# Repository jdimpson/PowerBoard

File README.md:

# PowerBoard Redux PCB

These are the Eage CAD Schematics and Board files, plus the Gerbers of some boards as-built, of an AdaFruit PowerBoost 1000C (https://www.adafruit.com/product/2465) adapted to the Raspberry Pi Zero form factor. It provides power to the +5VDC pins of the RPi header (protected via Schottkey diode). As AdaFruit describes the product this is based on, "With a built-in load-sharing battery charger circuit, you'll be able to keep your power-hungry project running even while recharging the battery!"

See also the PowerHolder board (https://github.com/jdimpson/PowerHolder) which is just like this one, but has battery clips to hold a Li Ion 18650 cell on the board, rather than fussing with JST connectors. It also provides a way to use a stock PowerBoost 10000C board so you don't have as much soldering to do.

The board patches the Low Battery (LBO) signal to the Pi via a level shifter, and also adds a programmable tactile button and LED.  You can use either one of those ubiquitous square tactile / momentary buttons, or one that mounts vertically (https://www.digikey.com/product-detail/en/te-connectivity-alcoswitch-switches/1825027-5/450-1662-ND/529484). The footprints for the two buttons overlap, which looks ugly and means you really can choose only one. It also provides a spot for a vertical slide switch that enables or disables the power circuit (https://www.digikey.com/product-detail/en/c-k/OS102011MA1QN1/CKN9559-ND/1981430). It's possible to find horizontal slide switch that fits in the same footprint. (I've only ordered them from ebay.)

Python software that works with the LBO signal, button, and LED are available in the [RPiIoT](https://github.com/jdimpson/RPiIoT) repo.

The MicroUSB connector is not the same foot print as AdaFruit uses in their PowerBoost, because I couldn't figure out which one it was. The part I use is an amphenol 10118194-0001LF (https://www.digikey.com/product-detail/en/amphenol-icc-fci/10118194-0001LF/609-4618-1-ND/2785382). It still has 4 through-hole-ish studs for strength (but can be hot-air reflowed) like AdaFruit's part, but the location of the studs are incompatible.

Battery is connected to a JST-style connector in a manner compatible with how AdaFruit does their polarity, or you can omit the connector and use the 2.54 mm pitch througholes to solder wires or a different connector to. Note that another Repo contains the PowerCarrier board, which is functionally identical to this board, but includes battery holders for a Li-Ion 18650 cell on the board.

Changelog
- Before v1.0 / Redux, I didn't know what I was doing, and kept laying out boards with traces that were way too small for the currents involved. 
- v1.01: Thickened VBAT, VLIPO, and USB traces from circuit to aux header; added zener diode to 5V trace into RPi; using VBAT rather than VLIPO in ENABLE pin switch. 

TODO:
- do over that preserve original PowerBoost footprint so that you can either reflow the board or just pop one of AdaFruit's board onto it. 

Raspberry Pi Pins used:

- GPIO17/Phy11 is connected to a momentary / tactile switch. Available for arbitrary software control (typically running my powerboard.py and associated code).
- GPIO27/Phy13 is connected to a resistor and then an LED. Available for arbitrary software control (e.g. flashing to show grace period, and typically running my powerboard.py and associated code).
- GPIO26/Phy37 is connected to via transistor and appropriate hold up resistor to the LBO signal of the PowerBoost circuit. This is how the Raspberry Pi knows to shut down. The signal is held at battery level (but level shifted to 3.3 V before hitting the RPi) until the Li Ion battery level drops below 3.4VDC (or maybe it's 3.2V, I forget) at which point the LBO signal drops to ground. This tells the software on the RPi to do a graceful shutdown.

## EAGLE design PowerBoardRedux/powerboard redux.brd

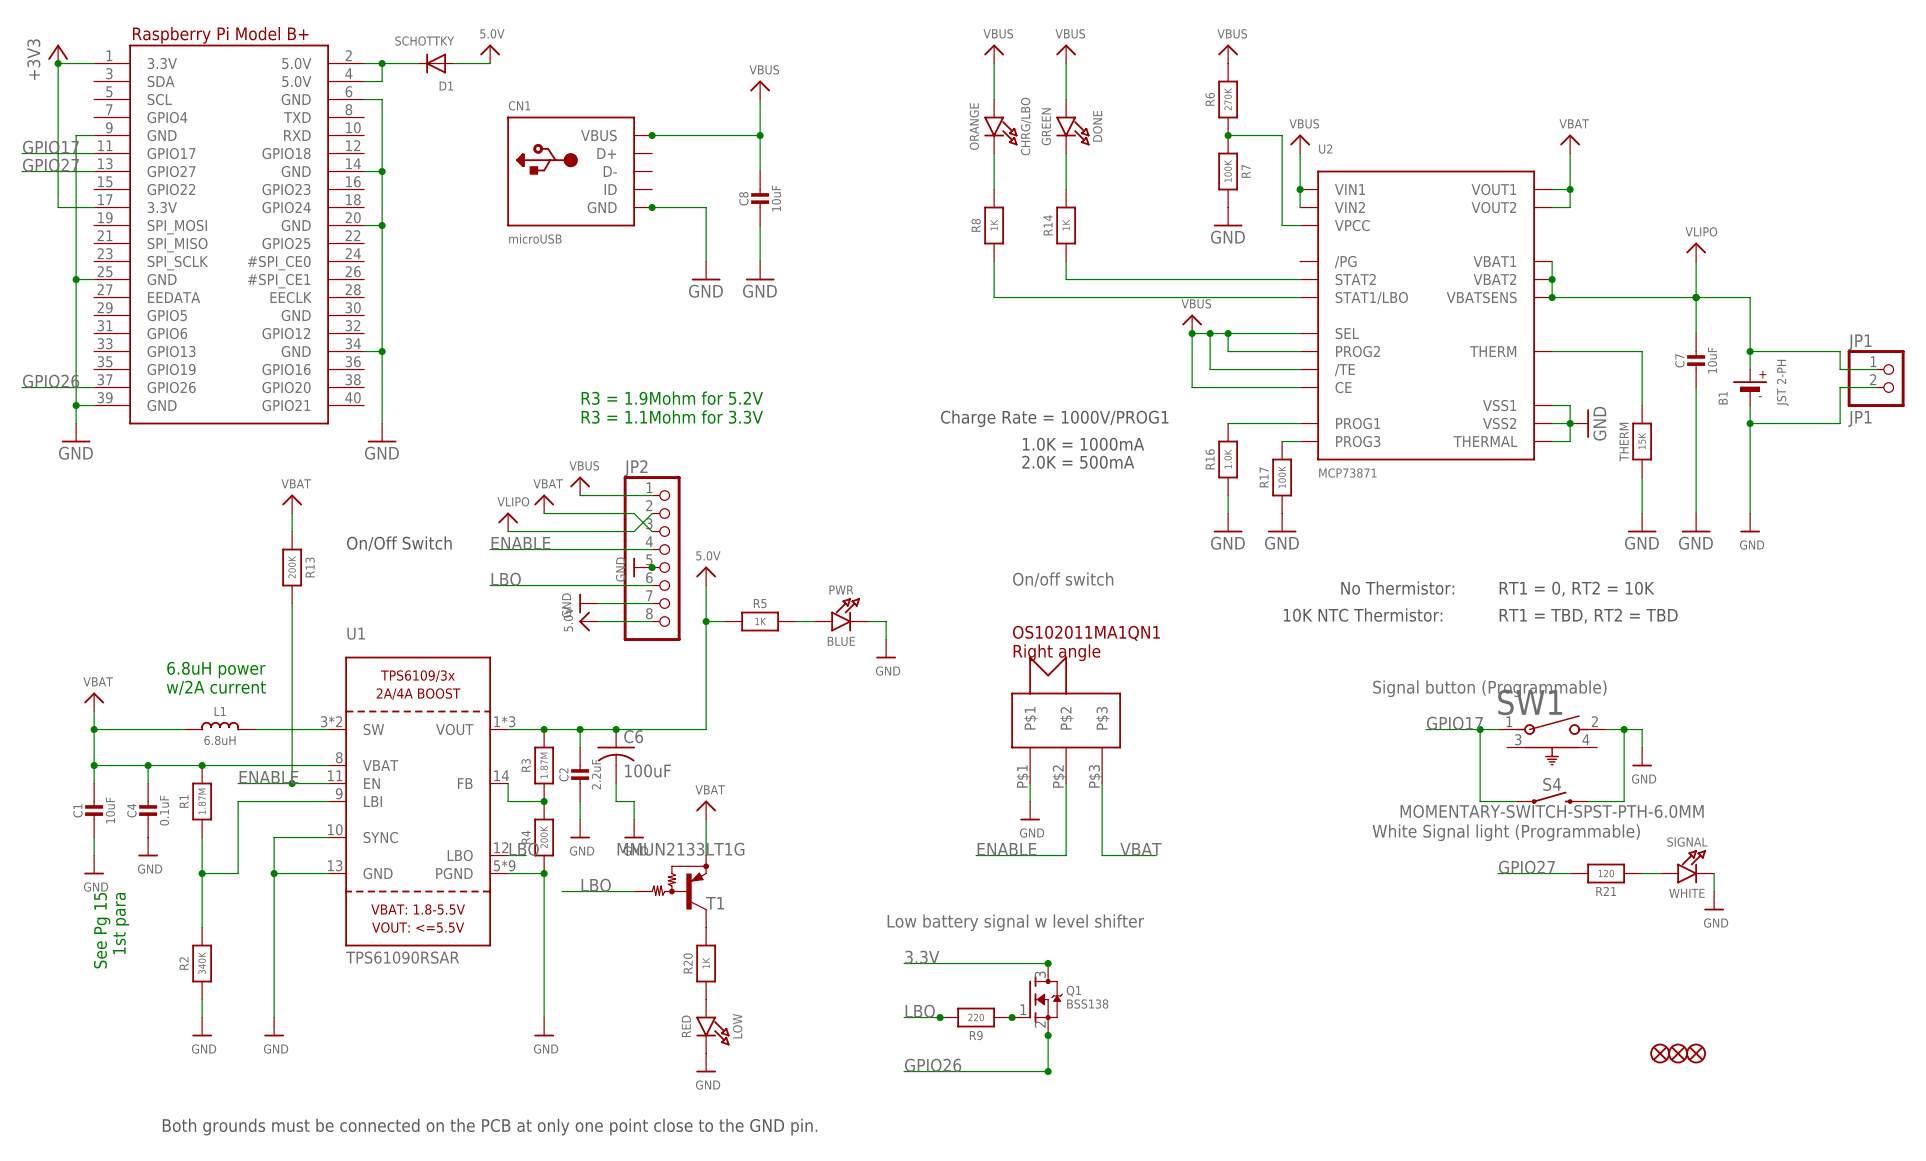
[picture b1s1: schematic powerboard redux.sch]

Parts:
B1: JST 2-PH; JSTPH2
C1, C7, C8: 10uF; 0805-NO@1
C2: 2.2uF; 0805-NO@1
C4: 0.1uF; 0805_10MGAP
C6: 100uF; C1210
CHRG/LBO: ORANGE; CHIPLED_0805_NOOUTLINE
CN1: microUSB; 4UCONN_20329
D1: SCHOTTKY; SOD-123FL
DONE: GREEN; CHIPLED_0805_NOOUTLINE
FID1, FID2, FID3: FIDUCIAL""; FIDUCIAL_1MM
JP1: JP1; 1X02_ROUND
JP2: HEADER-1X8ROUND; 1X08_ROUND
L1: 6.8uH; INDUCTOR_5X5MM_TDK_VLC5045
LOW: RED; CHIPLED_0805_NOOUTLINE
PWR: BLUE; CHIPLED_0805_NOOUTLINE
Q1: BSS138; SOT23-R
R1: 1.87M; _0805MP
R2: 340K; _0805MP
R3: 1.87M; 0805-NO
R4, R13: 200K; 0805-NO
R5, R8, R14, R20: 1K; 0805-NO
R6: 270K; 0805-NO
R7, R17: 100K; 0805-NO
R9: 220; 0805-NO
R16: 1.0K; 0805-NO
R21: 120; 0805-NO
RPI1: RASPBERRYPI_BPLUS_BONNETNODIM; PI_BONNET_NODIM
S4: MOMENTARY-SWITCH-SPST-PTH-6.0MM; TACTILE_SWITCH_PTH_6.0MM
SIGNAL: WHITE; CHIPLED_0805_NOOUTLINE
SW1: 1825027-5; SW2_1825027-A
SW2: OS102011MA1QN1
T1: MMUN2133LT1G; SC59-BEC
THERM: 15K; 0805-NO
U1: TPS61090RSAR; PVQFN-16
U2: MCP73871; QFN20_4MM

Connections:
3.3V: Q1.3 (D), RPI1.1 (3.3V), RPI1.17 (3.3V)
5.0V: C2.1, C6.1, D1.A, JP2.8, R3.2, R5.1, U1.1 (VOUT), U1.15 (VOUT), U1.16 (VOUT)
5.0V@1: D1.C, RPI1.2 (5.0V), RPI1.4 (5.0V)
ENABLE: JP2.4, R13.2, SW2.P$2, U1.11 (EN)
GND: B1.1 (-), C1.2, C2.2, C4.2, C6.2, C7.2, C8.2, CN1.BASE@1 (GND), CN1.BASE@2 (GND), CN1.GND, CN1.SPRT@1 (GND), CN1.SPRT@2 (GND), CN1.SPRT@3 (GND), CN1.SPRT@4 (GND), JP1.2, JP2.5, JP2.7, LOW.C, PWR.C, R2.1, R4.1, R7.2, R16.1, R17.1, RPI1.6 (GND), RPI1.9 (GND), RPI1.14 (GND), RPI1.20 (GND), RPI1.25 (GND), RPI1.30 (GND), RPI1.34 (GND), RPI1.39 (GND), S4.3 (2), SIGNAL.C, SW1.2, SW2.P$1, THERM.1, U1.5 (PGND), U1.6 (PGND), U1.7 (PGND), U1.10 (SYNC), U1.13 (GND), U1.P$18 (PGND), U1.P$19 (PGND), U1.P$20 (PGND), U1.P$21 (PGND), U1.P$22 (PGND), U1.THERMAL (PGND), U2.P$10 (VSS1), U2.P$11 (VSS2), U2.P$21 (THERMAL)
GPIO17: RPI1.11 (GPIO17), S4.1, SW1.1
GPIO26: Q1.2 (S), RPI1.37 (GPIO26)
GPIO27: R21.2, RPI1.13 (GPIO27)
LBO: JP2.6, R9.2, T1.B, U1.12 (LBO)
unnamed: L1.P$2 (2), U1.3 (SW), U1.4 (SW)
unnamed: LOW.A, R20.1
unnamed: R1.1, R2.2, U1.9 (LBI)
unnamed: PWR.A, R5.2
unnamed: R3.1, R4.2, U1.14 (FB)
unnamed: R20.2, T1.C
unnamed: R6.1, R7.1, U2.P$2 (VPCC)
unnamed: DONE.C, R14.2
unnamed: R14.1, U2.P$7 (STAT2)
unnamed: THERM.2, U2.P$5 (THERM)
unnamed: R8.1, U2.P$8 (STAT1/LBO)
unnamed: CHRG/LBO.C, R8.2
unnamed: R17.2, U2.P$12 (PROG3)
unnamed: Q1.1 (G), R9.1
unnamed: R21.1, SIGNAL.A
unnamed: R16.2, U2.P$13 (PROG1)
VBAT: C1.1, C4.1, JP2.3, L1.P$1 (1), R1.2, R13.1, SW2.P$3, T1.E, U1.8 (VBAT), U2.P$1 (VOUT1), U2.P$20 (VOUT2)
VBUS: C8.1, CHRG/LBO.A, CN1.VBUS, DONE.A, JP2.1, R6.2, U2.P$3 (SEL), U2.P$4 (PROG2), U2.P$9 (/TE), U2.P$17 (CE), U2.P$18 (VIN1), U2.P$19 (VIN2)
VLIPO: B1.2 (+), C7.1, JP1.1, JP2.2, U2.P$14 (VBAT1), U2.P$15 (VBAT2), U2.P$16 (VBATSENS)

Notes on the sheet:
Both grounds must be connected on the PCB at only one point close to the GND pin.
On/Off Switch
See Pg 15 1st para
6.8uH power w/2A current
R3 = 1.9Mohm for 5.2V R3 = 1.1Mohm for 3.3V
Charge Rate = 1000V/PROG1
1.0K = 1000mA
2.0K = 500mA
No Thermistor:
10K NTC Thermistor:
RT1 = 0, RT2 = 10K
RT1 = TBD, RT2 = TBD
Low battery signal w level shifter
On/off switch
Signal button (Programmable)
White Signal light (Programmable)

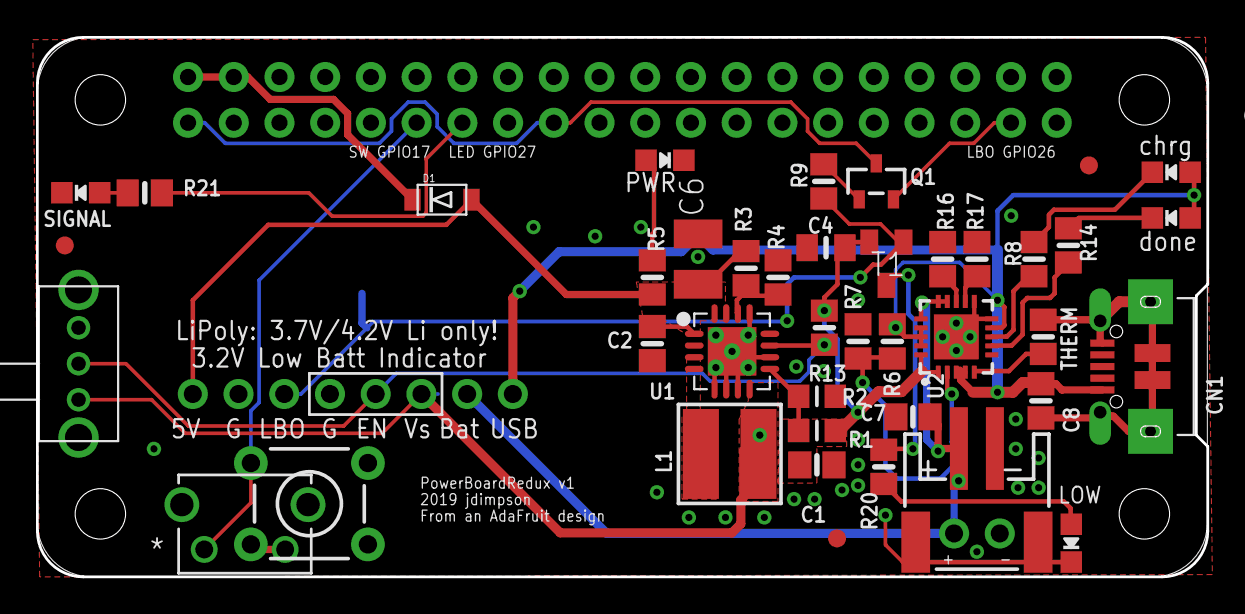
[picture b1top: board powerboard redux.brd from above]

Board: 2 copper layers, 65.0 x 30.0 mm, 44 parts (0 on the bottom side), 28 nets.

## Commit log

2020-09-07 Fixed typo ref to Adafruit's powerboost
2020-09-07 Having trouble with SVG ULP script.
    Still not happy with it.
2020-09-07 Added record of RPi pins used.
2020-09-07 Described battery attachment
2020-09-07 more description
2020-09-07 typos
2020-09-07 Managed to make board & schematic inconsistent, fixed
2020-09-07 schottkey not zener
2020-09-07 Cleanup for BOM upload
2020-09-07 Refernce to PowerHolder
2020-09-08 Oh so the pound sign given in the default readme files isn't a comment...
2020-09-09 link to image
2020-09-09 link to python repo

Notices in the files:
parts and their libraries:
microbuilder: This work is placed in the public domain, and may be freely used for commercial and non-commercial work with the following conditions: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
SparkFun-Switches: Licensing: Creative Commons ShareAlike 4.0 International - https://creativecommons.org/licenses/by-sa/4.0
